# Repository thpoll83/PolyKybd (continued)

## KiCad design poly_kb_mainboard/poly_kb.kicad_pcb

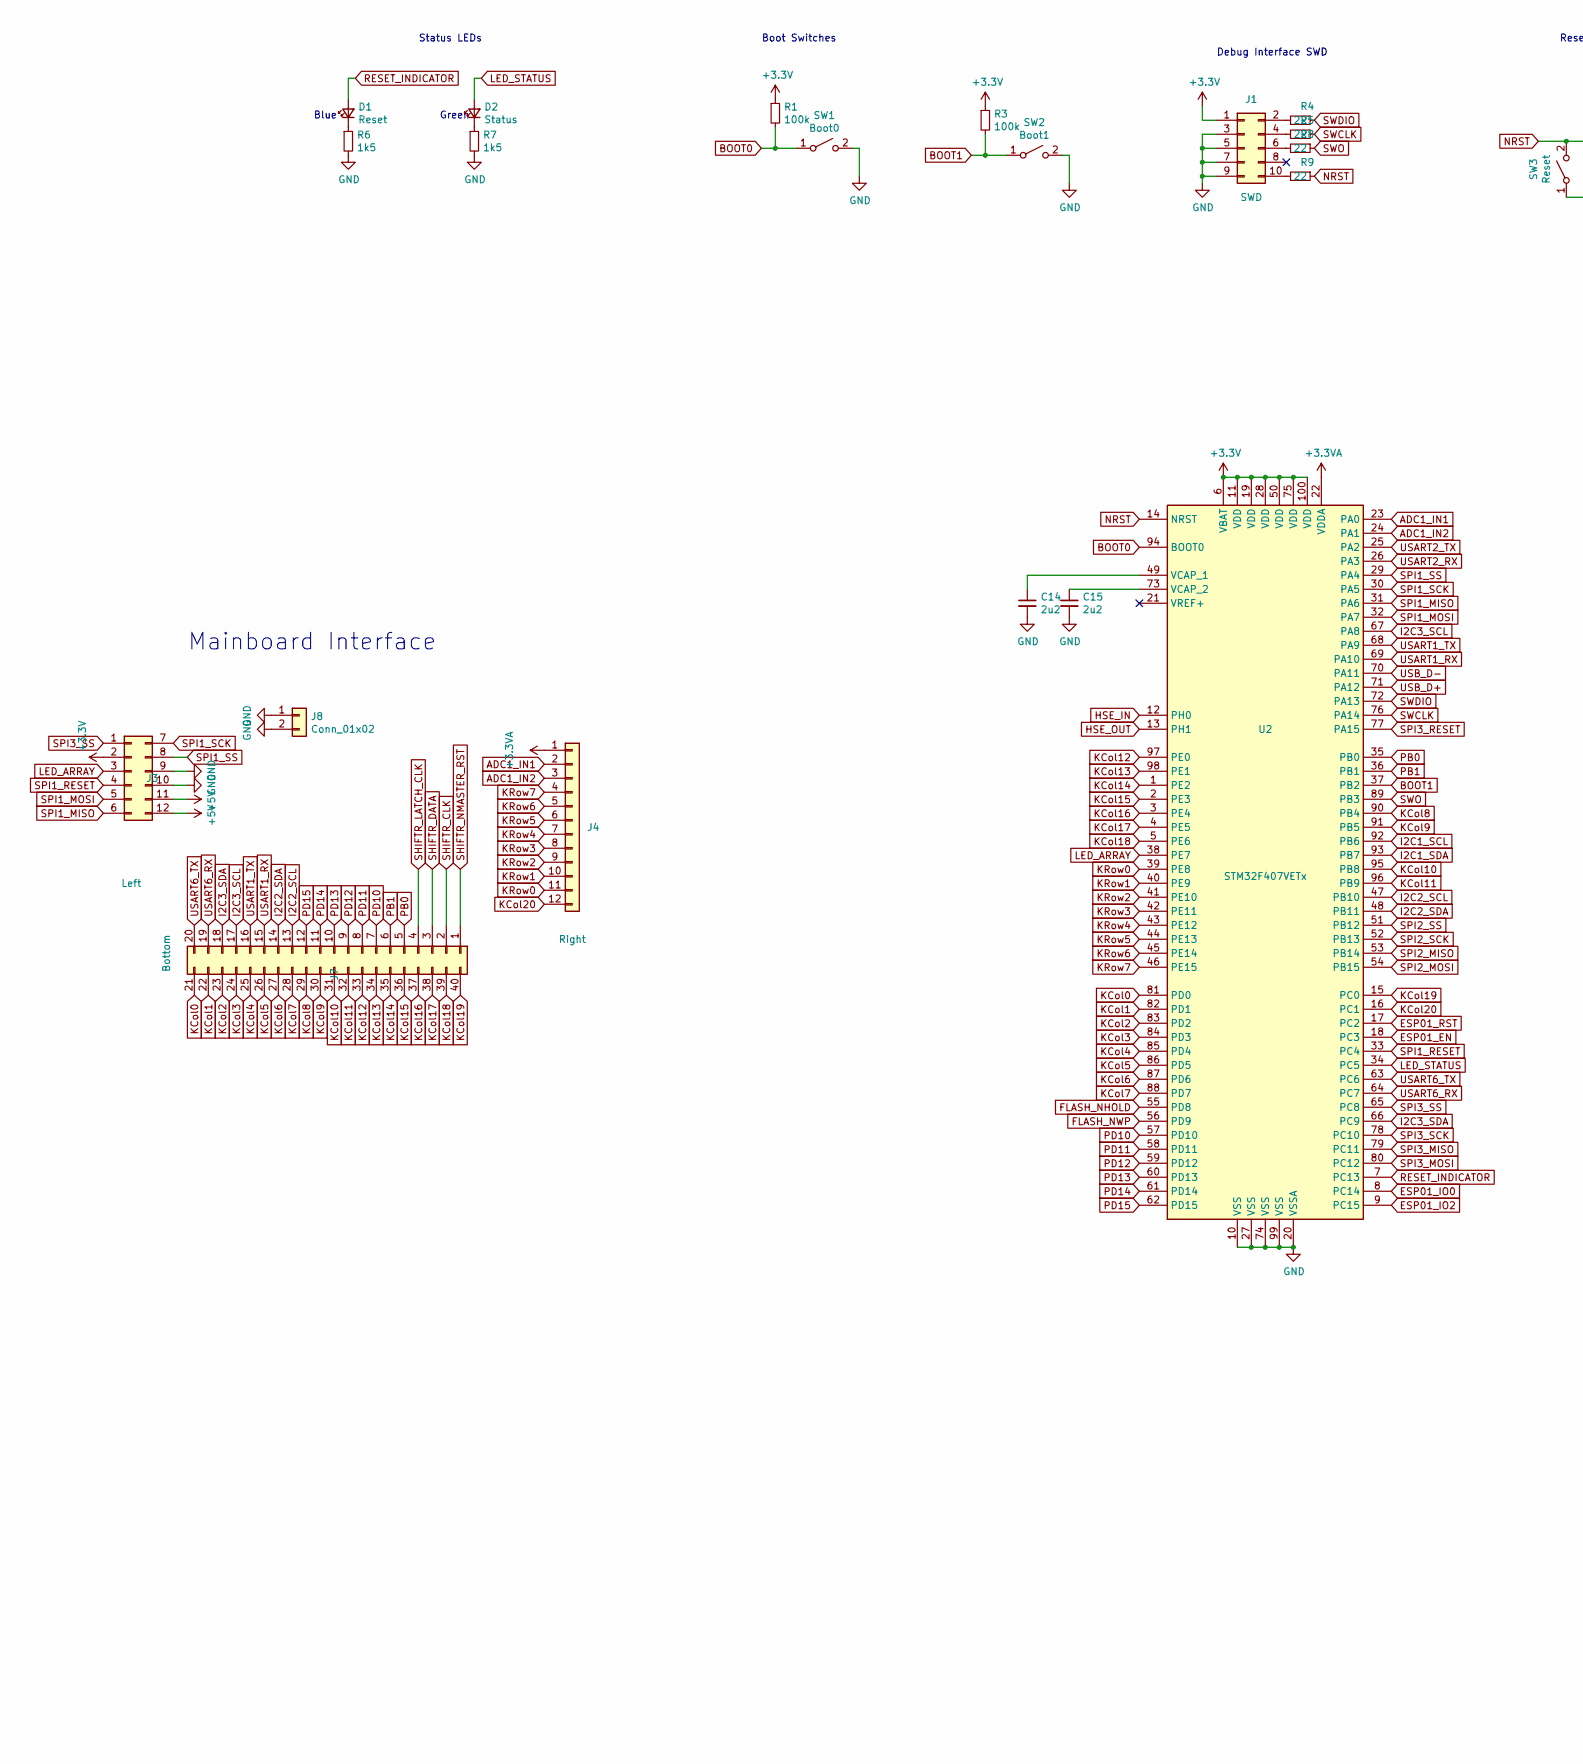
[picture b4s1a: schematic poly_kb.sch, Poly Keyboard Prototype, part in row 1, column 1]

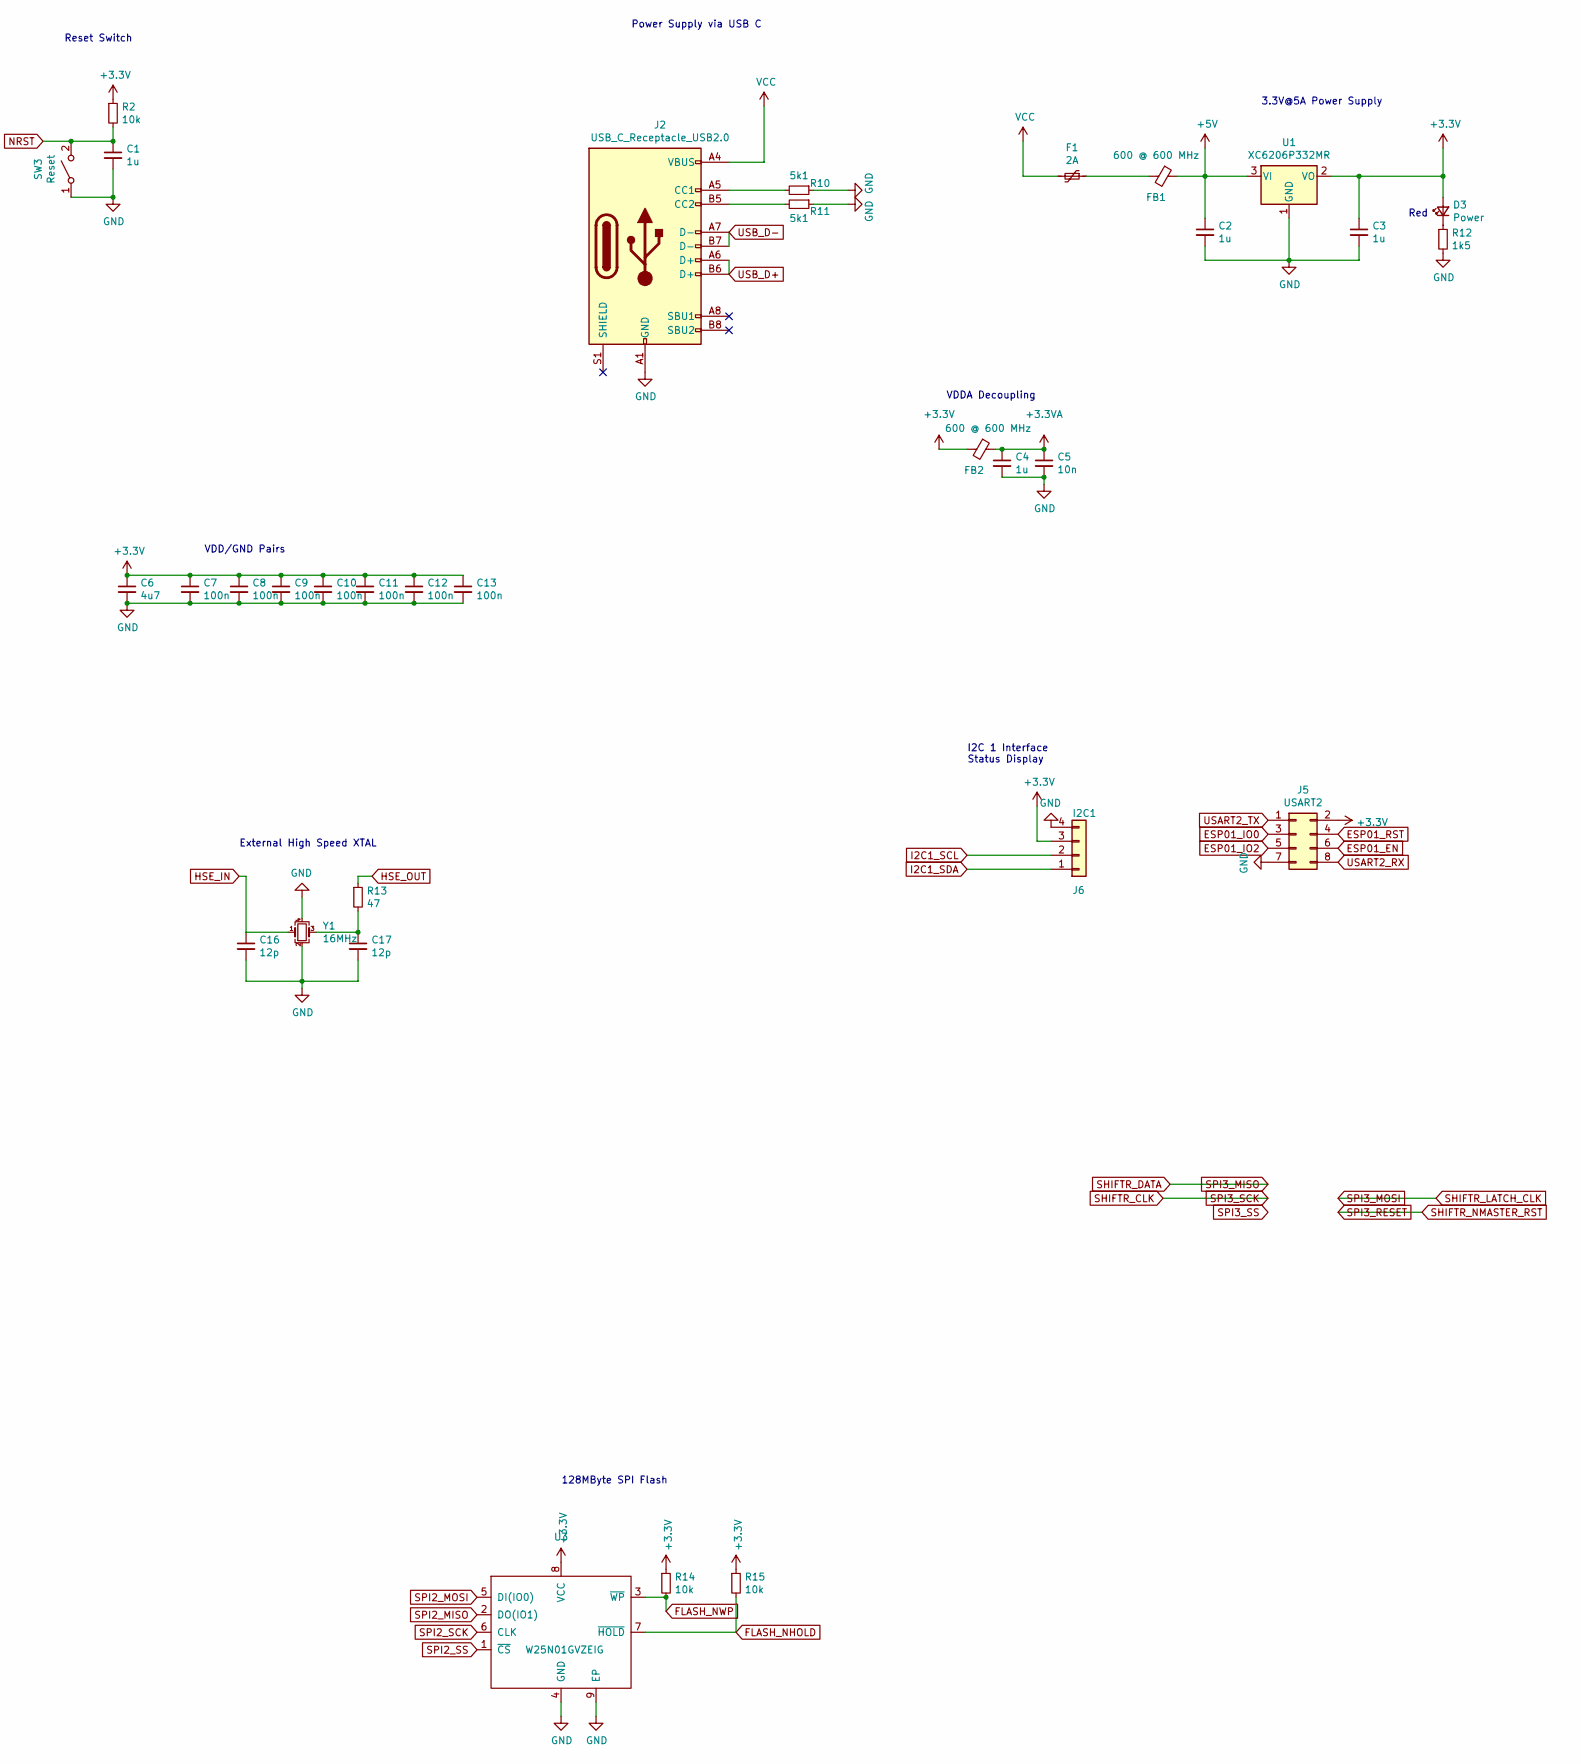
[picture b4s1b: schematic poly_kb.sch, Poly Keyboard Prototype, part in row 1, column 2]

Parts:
C1, C2, C3, C4: 1u; C_0402_1005Metric; LCSC C52923
C5: 10n; C_0402_1005Metric; LCSC C15195
C6: 4u7; C_0603_1608Metric; LCSC C19666
C7, C8, C9, C10, C11, C12, C13: 100n; C_0402_1005Metric; LCSC C1525
C14, C15: 2u2; C_0603_1608Metric; LCSC C23630
C16, C17: 12p; C_0402_1005Metric; LCSC C1547
D1: Reset; LED_0603_1608Metric; LCSC C72041
D2: Status; LED_0603_1608Metric; LCSC C72043
D3: Power; LED_0603_1608Metric; LCSC C2286
F1: 2A; Fuse_1206_3216Metric; LCSC C70085
FB1, FB2: 600 @ 600 MHz; L_0805_2012Metric; LCSC C1017
J1: SWD; SIDE-SWD
J2: USB_C_Receptacle_USB2.0; USB_C_Receptacle_HRO_TYPE-C-31-M-12; LCSC C165948
J3: Left; PinHeader_2x06_P2.54mm_Vertical; LCSC C225521
J4: Right; PinHeader_1x12_P2.54mm_Vertical; LCSC C225487
J5: USART2; PinHeader_2x04_P2.54mm_Vertical; LCSC C541854
J6: I2C1; PinHeader_1x04_P2.54mm_Vertical; LCSC C225501
J7: Bottom; PinHeader_2x20_P2.54mm_Vertical; LCSC C124383
J8: Conn_01x02; PinHeader_1x02_P2.54mm_Vertical; LCSC C464599
R1, R3: 100k; R_0402_1005Metric; LCSC C25741
R2, R14, R15: 10k; R_0402_1005Metric; LCSC C25744
R4, R5, R8, R9: 22; R_0402_1005Metric; LCSC C25092
R6, R7, R12: 1k5; R_0402_1005Metric; LCSC C25867
R10, R11: 5k1; R_0402_1005Metric; LCSC C25905
R13: 47; R_0402_1005Metric; LCSC C25118
SW1: Boot0; SW_SPST_B3U-3000P-B; LCSC C963349
SW2: Boot1; SW_SPST_B3U-3000P-B; LCSC C963349
SW3: Reset; SW_SPST_B3U-3000P-B; LCSC C963349
U1: XC6206P332MR; SOT-23; LCSC C5446
U2: STM32F407VETx; LQFP-100_14x14mm_P0.5mm; LCSC C28730
U3: W25N01GVZEIG; LCSC C88868
Y1: 16MHz; Crystal_SMD_3225-4Pin_3.2x2.5mm; LCSC C13738

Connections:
+3.3VA: C4.1, C5.1, FB2.1, J4.1, U2.22 (VDDA)
+3V3: C3.1, C6.1, C7.1, C8.1, C9.1, C10.1, C11.1, C12.1, C13.1, D3.2 (A), FB2.2, J1.1, J3.2, J5.2, J6.3, R1.1, R2.1, R3.1, R14.1, R15.1, U1.2 (VO), U2.6 (VBAT), U2.11 (VDD), U2.19 (VDD), U2.28 (VDD), U2.50 (VDD), U2.75 (VDD), U2.100 (VDD), U3.8 (VCC)
+5V: C2.1, FB1.1, J3.11, J3.12, U1.3 (VI)
ADC1_IN1: J4.2, U2.23 (PA0)
ADC1_IN2: J4.3, U2.24 (PA1)
BOOT0: R1.2, SW1.1 (A), U2.94 (BOOT0)
BOOT1: R3.2, SW2.1 (A), U2.37 (PB2)
ESP01_EN: J5.6, U2.18 (PC3)
ESP01_IO0: J5.3, U2.8 (PC14)
ESP01_IO2: J5.5, U2.9 (PC15)
ESP01_RST: J5.4, U2.17 (PC2)
FLASH_NHOLD: R15.2, U2.55 (PD8), U3.7 (~HOLD)
FLASH_NWP: R14.2, U2.56 (PD9), U3.3 (~WP)
GND: C1.2, C2.2, C3.2, C4.2, C5.2, C6.2, C7.2, C8.2, C9.2, C10.2, C11.2, C12.2, C13.2, C14.2, C15.2, C16.2, C17.2, J1.3, J1.5, J1.7, J1.9, J2.A1 (GND), J2.A12 (GND), J2.B1 (GND), J2.B12 (GND), J3.9, J3.10, J5.7, J6.4, J8.1, J8.2, R6.2, R7.2, R10.1, R11.1, R12.2, SW1.2 (B), SW2.2 (B), SW3.1 (A), U1.1 (GND), U2.10 (VSS), U2.20 (VSSA), U2.27 (VSS), U2.74 (VSS), U2.99 (VSS), U3.4 (GND), U3.9 (EP), Y1.2, Y1.4
HSE_IN: C16.1, U2.12 (PH0), Y1.1
HSE_OUT: R13.1, U2.13 (PH1)
I2C1_SCL: J6.2, U2.92 (PB6)
I2C1_SDA: J6.1, U2.93 (PB7)
I2C2_SCL: J7.13, U2.47 (PB10)
I2C2_SDA: J7.14, U2.48 (PB11)
I2C3_SCL: J7.17, U2.67 (PA8)
I2C3_SDA: J7.18, U2.66 (PC9)
KCol0: J7.21, U2.81 (PD0)
KCol1: J7.22, U2.82 (PD1)
KCol2: J7.23, U2.83 (PD2)
KCol3: J7.24, U2.84 (PD3)
KCol4: J7.25, U2.85 (PD4)
KCol5: J7.26, U2.86 (PD5)
KCol6: J7.27, U2.87 (PD6)
KCol7: J7.28, U2.88 (PD7)
KCol8: J7.29, U2.90 (PB4)
KCol9: J7.30, U2.91 (PB5)
KCol10: J7.31, U2.95 (PB8)
KCol11: J7.32, U2.96 (PB9)
KCol12: J7.33, U2.97 (PE0)
KCol13: J7.34, U2.98 (PE1)
KCol14: J7.35, U2.1 (PE2)
KCol15: J7.36, U2.2 (PE3)
KCol16: J7.37, U2.3 (PE4)
KCol17: J7.38, U2.4 (PE5)
KCol18: J7.39, U2.5 (PE6)
KCol19: J7.40, U2.15 (PC0)
KCol20: J4.12, U2.16 (PC1)
KRow0: J4.11, U2.39 (PE8)
KRow1: J4.10, U2.40 (PE9)
KRow2: J4.9, U2.41 (PE10)
KRow3: J4.8, U2.42 (PE11)
KRow4: J4.7, U2.43 (PE12)
KRow5: J4.6, U2.44 (PE13)
KRow6: J4.5, U2.45 (PE14)
KRow7: J4.4, U2.46 (PE15)
LED_ARRAY: J3.3, U2.38 (PE7)
LED_STATUS: D2.2 (A), U2.34 (PC5)
NRST: C1.1, R2.2, R9.1, SW3.2 (B), U2.14 (NRST)
unnamed: C14.1, U2.49 (VCAP_1)
unnamed: C15.1, U2.73 (VCAP_2)
unnamed: C17.1, R13.2, Y1.3
unnamed: D1.1 (K), R6.1
unnamed: D2.1 (K), R7.1
unnamed: D3.1 (K), R12.1
unnamed: F1.1, FB1.2
unnamed: J1.2, R4.2
unnamed: J1.4, R5.2
unnamed: J1.6, R8.2
unnamed: J1.10, R9.2
unnamed: J2.A5 (CC1), R10.2
unnamed: J2.B5 (CC2), R11.2
PB0: J7.5, U2.35 (PB0)
PB1: J7.6, U2.36 (PB1)
PD10: J7.7, U2.57 (PD10)
PD11: J7.8, U2.58 (PD11)
PD12: J7.9, U2.59 (PD12)
PD13: J7.10, U2.60 (PD13)
PD14: J7.11, U2.61 (PD14)
PD15: J7.12, U2.62 (PD15)
RESET_INDICATOR: D1.2 (A), U2.7 (PC13)
SHIFTR_CLK: J7.2, U2.78 (PC10)
SHIFTR_DATA: J7.3, U2.79 (PC11)
SHIFTR_LATCH_CLK: J7.4, U2.80 (PC12)
SHIFTR_NMASTER_RST: J7.1, U2.77 (PA15)
SPI1_MISO: J3.6, U2.31 (PA6)
SPI1_MOSI: J3.5, U2.32 (PA7)
SPI1_RESET: J3.4, U2.33 (PC4)
SPI1_SCK: J3.7, U2.30 (PA5)
SPI1_SS: J3.8, U2.29 (PA4)
SPI2_MISO: U2.53 (PB14), U3.2 (DO(IO1))
SPI2_MOSI: U2.54 (PB15), U3.5 (DI(IO0))
SPI2_SCK: U2.52 (PB13), U3.6 (CLK)
SPI2_SS: U2.51 (PB12), U3.1 (~CS)
SPI3_SS: J3.1, U2.65 (PC8)
SWCLK: R5.1, U2.76 (PA14)
SWDIO: R4.1, U2.72 (PA13)
SWO: R8.1, U2.89 (PB3)
USART1_RX: J7.15, U2.69 (PA10)
USART1_TX: J7.16, U2.68 (PA9)
USART2_RX: J5.8, U2.26 (PA3)
USART2_TX: J5.1, U2.25 (PA2)
USART6_RX: J7.19, U2.64 (PC7)
USART6_TX: J7.20, U2.63 (PC6)
USB_D+: J2.A6 (D+), J2.B6 (D+), U2.71 (PA12)
USB_D-: J2.A7 (D-), J2.B7 (D-), U2.70 (PA11)
VCC: F1.2, J2.A4 (VBUS), J2.A9 (VBUS), J2.B4 (VBUS), J2.B9 (VBUS)

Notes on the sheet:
VDDA Decoupling
External High Speed XTAL
Boot Switches
VDD/GND Pairs
Status LEDs
3.3V@5A Power Supply
Debug Interface SWD
I2C 1 Interface Status Display
Green
Power Supply via USB C
Reset Switch
Blue
Red
128MByte SPI Flash
Mainboard Interface

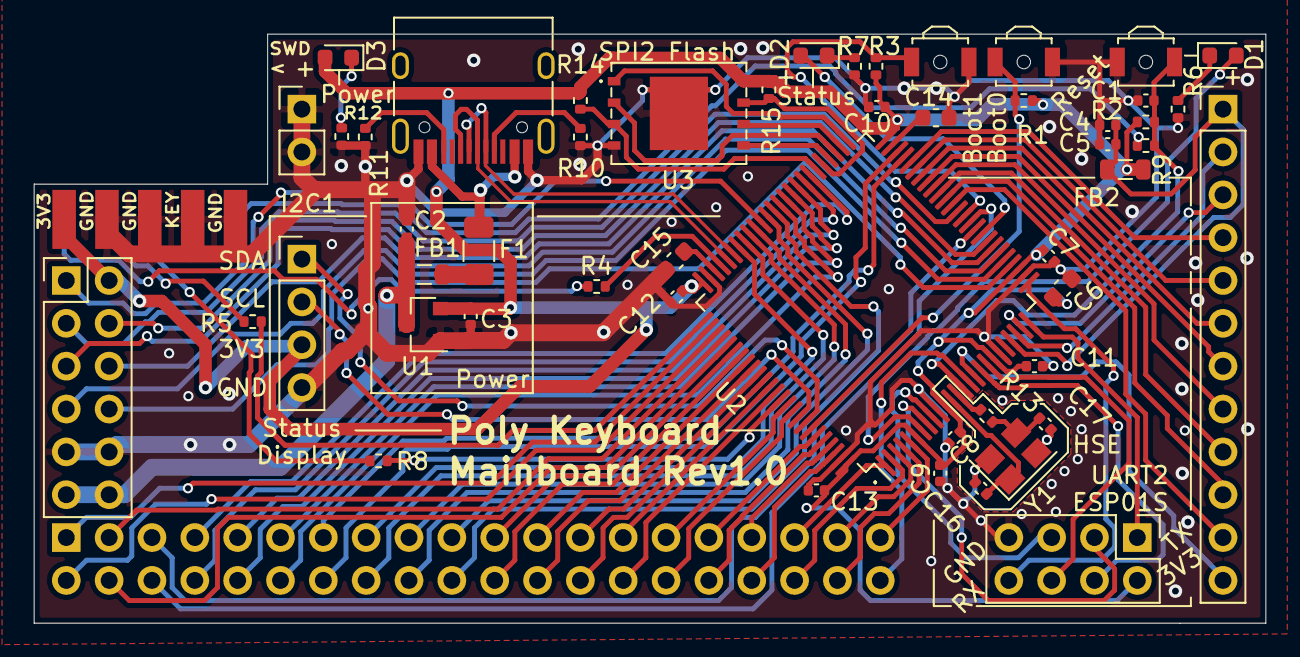
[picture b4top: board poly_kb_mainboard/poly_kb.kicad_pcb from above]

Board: 2 copper layers, 73.0 x 34.9 mm, 53 parts (1 on the bottom side), 102 nets.

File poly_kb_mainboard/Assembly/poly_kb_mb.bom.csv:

Designator,Quantity,Value,Footprint,LCSC Part #,Comment
"C1, C2, C3, C4",4,1u,C_0402_1005Metric,C52923," Unpolarized capacitor, small symbol"
C5,1,10n,C_0402_1005Metric,C15195," Unpolarized capacitor, small symbol"
C6,1,4u7,C_0603_1608Metric,C19666," Unpolarized capacitor, small symbol"
"C7, C8, C9, C10, C11, C12, C13",7,100n,C_0402_1005Metric,C1525," Unpolarized capacitor, small symbol"
"C14, C15",2,2u2,C_0603_1608Metric,C23630," Unpolarized capacitor, small symbol"
"C16, C17",2,12p,C_0402_1005Metric,C1547," Unpolarized capacitor, small symbol"
D1,1,Reset,LED_0603_1608Metric,C72041," Light emitting diode, small symbol"
D2,1,Status,LED_0603_1608Metric,C72043," Light emitting diode, small symbol"
D3,1,Power,LED_0603_1608Metric,C2286," Light emitting diode, small symbol"
F1,1,2A,Fuse_1206_3216Metric,C70085," Resettable fuse, polymeric positive temperature coefficient, small symbol"
"FB1, FB2",2,600 @ 600 MHz,L_0805_2012Metric,C1017," Ferrite bead, small symbol"
J1,1,SWD,SIDE-SWD,," Generic connector, double row, 02x05, odd/even pin numbering scheme (row 1 odd numbers, row 2 even numbers), script generated (kicad-library-utils/schlib/autogen/connector/)"
J2,1,USB_C_Receptacle_USB2.0,USB_C_Receptacle_HRO_TYPE-C-31-M-12,C165948, USB 2.0-only Type-C Receptacle connector
J3,1,Left,PinHeader_2x06_P2.54mm_Vertical,C225521," Generic connector, double row, 02x06, top/bottom pin numbering scheme (row 1: 1...pins_per_row, row2: pins_per_row+1 ... num_pins), script generated (kicad-library-utils/schlib/autogen/connector/)"
J4,1,Right,PinHeader_1x12_P2.54mm_Vertical,C225487," Generic connector, single row, 01x12, script generated (kicad-library-utils/schlib/autogen/connector/)"
J5,1,USART2,PinHeader_2x04_P2.54mm_Vertical,C541854," Generic connector, double row, 02x04, odd/even pin numbering scheme (row 1 odd numbers, row 2 even numbers), script generated (kicad-library-utils/schlib/autogen/connector/)"
J6,1,I2C1,PinHeader_1x04_P2.54mm_Vertical,C225501," Generic connector, single row, 01x04, script generated (kicad-library-utils/schlib/autogen/connector/)"
J7,1,Bottom,PinHeader_2x20_P2.54mm_Vertical,C124383," Generic connector, double row, 02x20, counter clockwise pin numbering scheme (similar to DIP packge numbering), script generated (kicad-library-utils/schlib/autogen/connector/)"
J8,1,Conn_01x02,PinHeader_1x02_P2.54mm_Vertical,C464599," Generic connector, single row, 01x02, script generated (kicad-library-utils/schlib/autogen/connector/)"
"R1, R3",2,100k,R_0402_1005Metric,C25741," Resistor, small symbol"
"R2, R14, R15",3,10k,R_0402_1005Metric,C25744," Resistor, small symbol"
"R4, R5, R8, R9",4,22,R_0402_1005Metric,C25092," Resistor, small symbol"
"R6, R7, R12",3,1k5,R_0402_1005Metric,C25867," Resistor, small symbol"
"R10, R11",2,5k1,R_0402_1005Metric,C25905," Resistor, small symbol"
R13,1,47,R_0402_1005Metric,C25118," Resistor, small symbol"
SW1,1,Boot0,SW_SPST_B3U-3000P-B,C963349, Single Pole Single Throw (SPST) switch
SW2,1,Boot1,SW_SPST_B3U-3000P-B,C963349, Single Pole Single Throw (SPST) switch
SW3,1,Reset,SW_SPST_B3U-3000P-B,C963349, Single Pole Single Throw (SPST) switch
U1,1,XC6206P332MR,SOT-23,C5446," Positive 60-250mA Low Dropout Regulator, Fixed Output, SOT-23"
U2,1,STM32F407VETx,LQFP-100_14x14mm_P0.5mm,C28730," ARM Cortex-M4 MCU, 512KB flash, 128KB RAM, 168MHz, 1.8-3.6V, 82 GPIO, LQFP-100"
U3,1,W25N01GVZEIG,W25N01GVZEIG,C88868, 
Y1,1,16MHz,Crystal_SMD_3225-4Pin_3.2x2.5mm,C13738," Four pin crystal, GND on pins 2 and 4, small symbol"

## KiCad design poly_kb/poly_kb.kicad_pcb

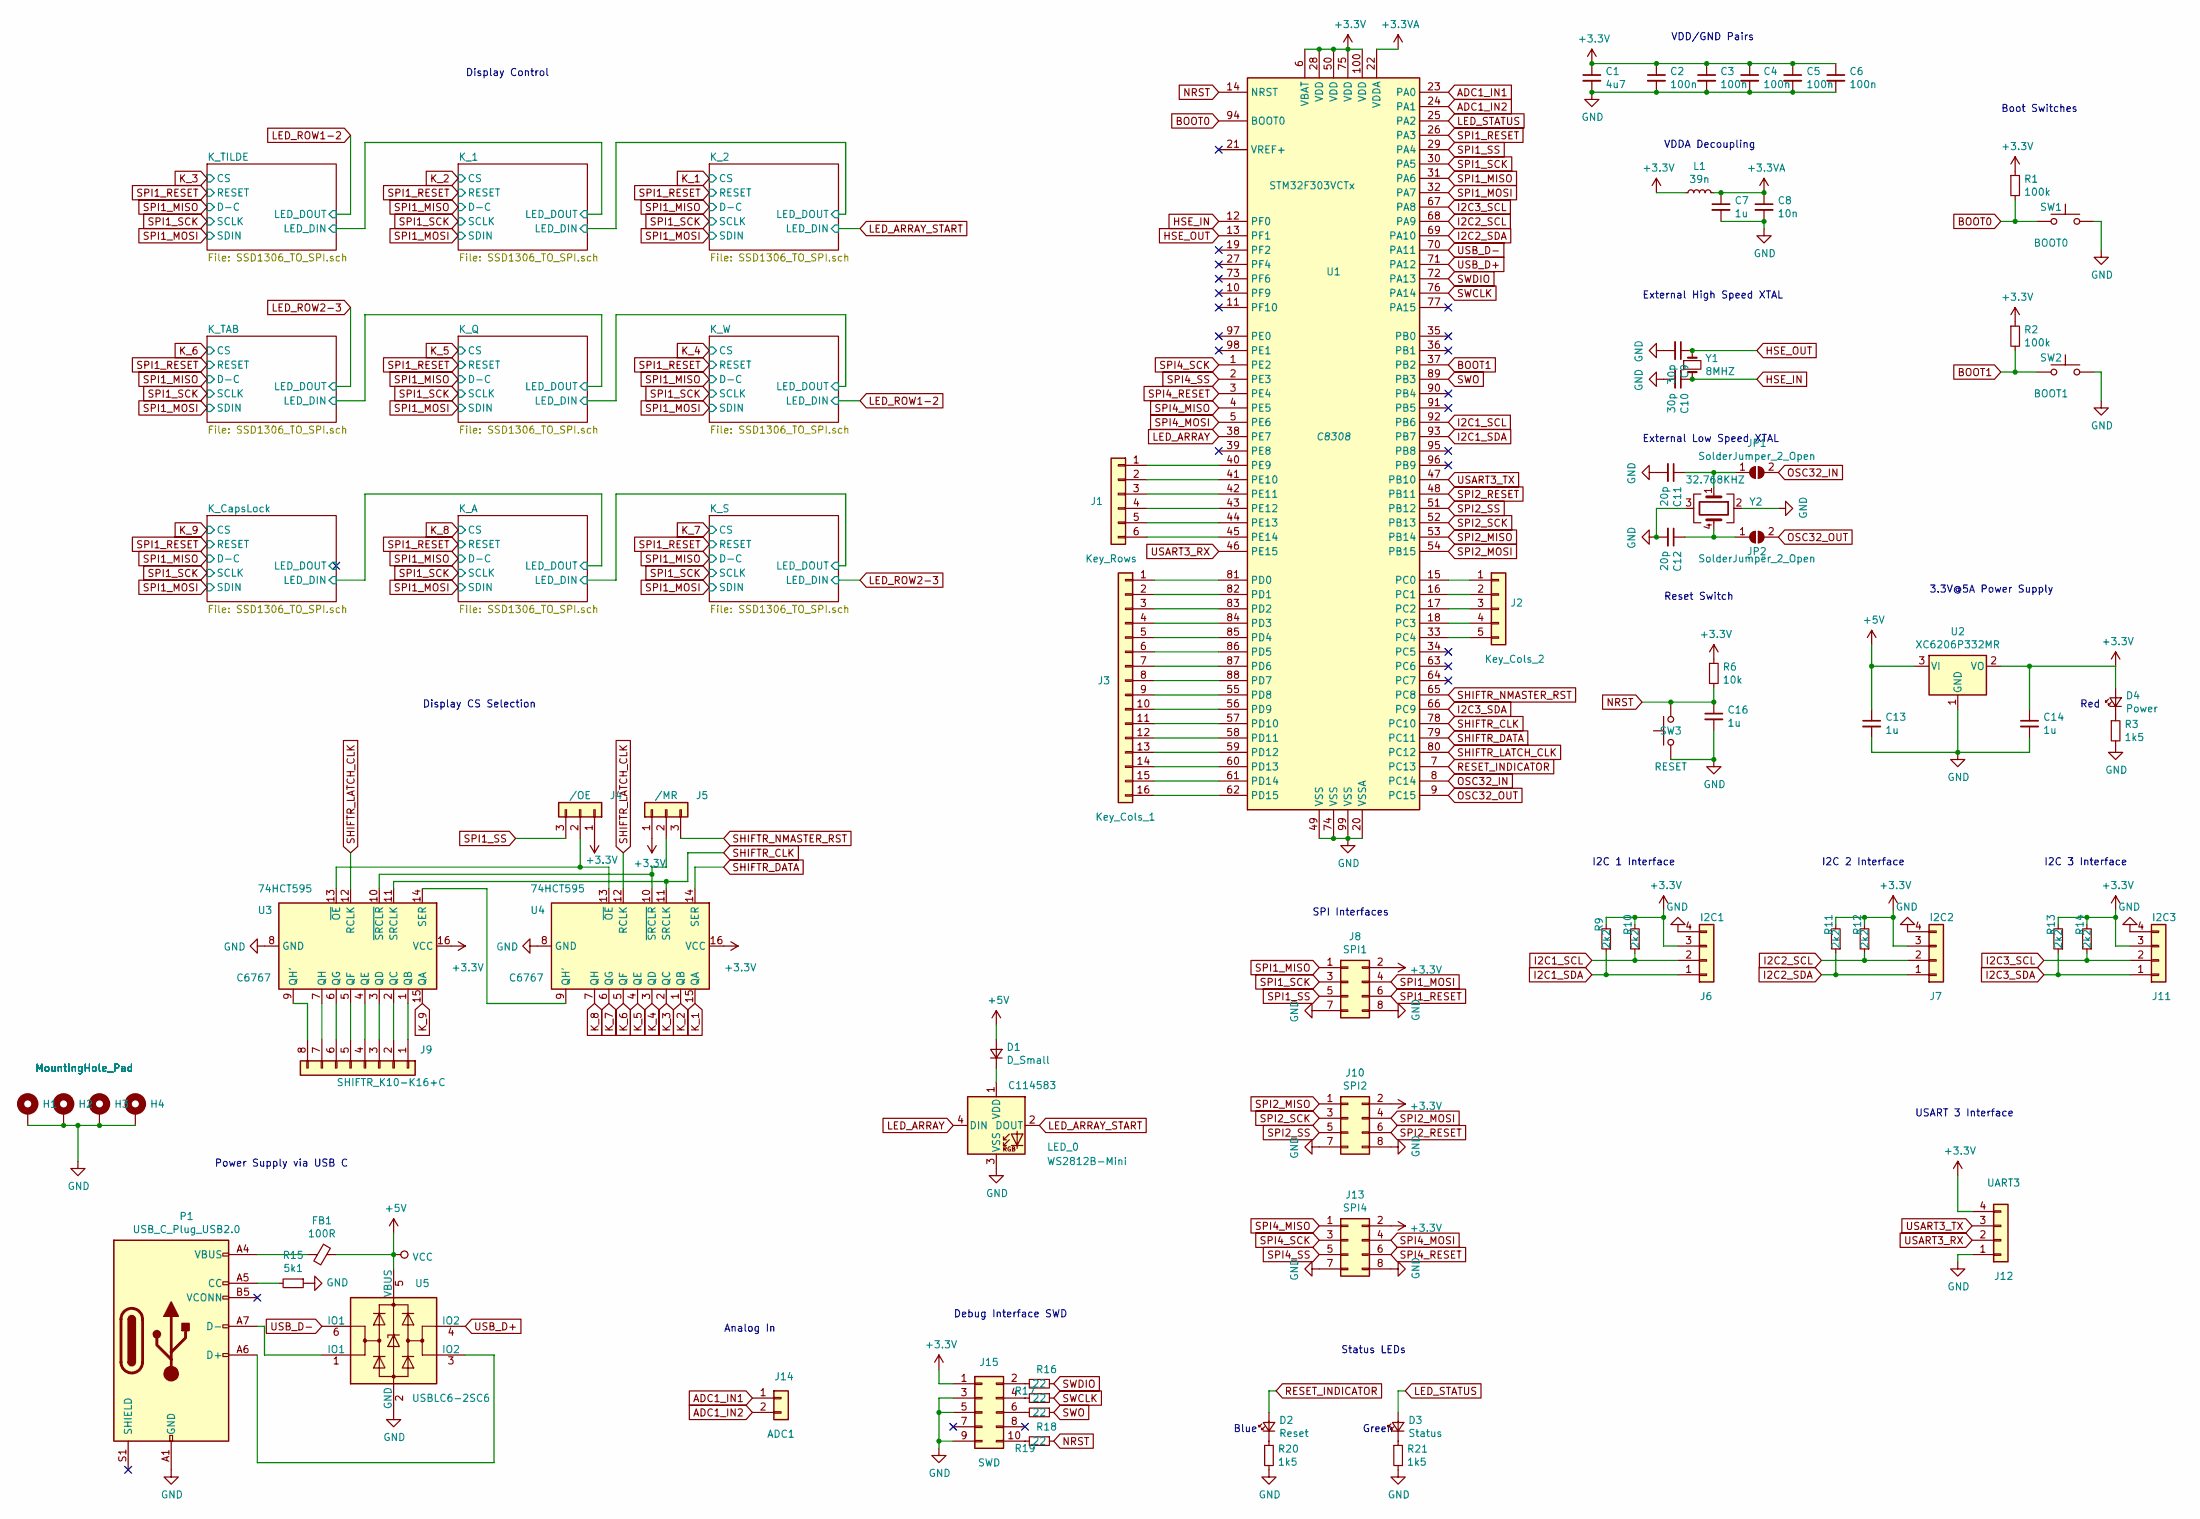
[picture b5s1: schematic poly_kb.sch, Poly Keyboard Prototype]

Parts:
C1: 4u7; C_0603_1608Metric; LCSC C19666
C2, C3, C4, C5, C6: 100n; C_0402_1005Metric; LCSC C1525
C7, C13, C14, C16: 1u; C_0402_1005Metric; LCSC C52923
C8: 10n; C_0402_1005Metric; LCSC C15195
C9, C10: 30p; C_0402_1005Metric; LCSC C1570
C11, C12: 20p; C_0603_1608Metric; LCSC C1603
D1: D_Small; D_SOD-123F; LCSC C64898
D2: Reset; LED_0603_1608Metric; LCSC C72041
D3: Status; LED_0603_1608Metric; LCSC C72043
D4: Power; LED_0603_1608Metric; LCSC C2286
FB1: 100R; L_0805_2012Metric; LCSC C1015
H1, H2, H3, H4: MountingHole_Pad; MountingHole_4.3mm_M4_Pad_Via
J1: Key_Rows; PinHeader_1x06_P2.54mm_Vertical
J2: Key_Cols_2; PinHeader_1x05_P2.54mm_Vertical
J3: Key_Cols_1; PinHeader_1x16_P2.54mm_Vertical
J4: /OE; PinHeader_1x03_P2.54mm_Vertical
J5: /MR; PinHeader_1x03_P2.54mm_Vertical
J6: I2C1; PinHeader_1x04_P2.54mm_Vertical
J7: I2C2; PinHeader_1x04_P2.54mm_Vertical
J8: SPI1; PinHeader_2x04_P2.54mm_Vertical
J9: SHIFTR_K10-K16+C; PinHeader_1x08_P2.54mm_Vertical
J10: SPI2; PinHeader_2x04_P2.54mm_Vertical
J11: I2C3; PinHeader_1x04_P2.54mm_Vertical
J12: UART3; PinHeader_1x04_P2.54mm_Vertical
J13: SPI4; PinHeader_2x04_P2.54mm_Vertical
J14: ADC1; PinHeader_1x02_P2.54mm_Vertical
J15: SWD; PinHeader_2x05_P2.54mm_Vertical
JP1, JP2: SolderJumper_2_Open; SolderJumper-2_P1.3mm_Open_TrianglePad1.0x1.5mm
L1: 39n; L_0402_1005Metric; LCSC C26443
LED_0: WS2812B-Mini; LCSC C114583
P1: USB_C_Plug_USB2.0; USB_C_Receptacle_Palconn_UTC16-G; LCSC C393939
R1, R2: 100k; R_0603_1608Metric; LCSC C25803
R3, R20, R21: 1k5; R_0805_2012Metric; LCSC C4310
R6: 10k; R_0402_1005Metric; LCSC C25744
R9, R10, R11, R12, R13, R14: 2k2; R_0805_2012Metric; LCSC C17521
R15: 5k1; R_0603_1608Metric; LCSC C23186
R16, R17, R18, R19: 22; R_0805_2012Metric; LCSC C17561
SW1: BOOT0; Switch_THT
SW2: BOOT1; Switch_THT
SW3: RESET; Switch_THT
U1: STM32F303VCTx; LQFP-100_14x14mm_P0.5mm; LCSC C8308
U2: XC6206P332MR; SOT-23; LCSC C5446
U3, U4: 74HCT595; SOIC-16_3.9x9.9mm_P1.27mm; LCSC C6767
U5: USBLC6-2SC6; SOT-23-6; LCSC C7519
Y1: 8MHZ; Crystal_SMD_5032-2Pin_5.0x3.2mm; LCSC C115962
Y2: 32.768KHZ; SMD-0832_4P; LCSC C145166

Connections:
+3.3VA: C7.1, C8.1, L1.2, U1.22 (VDDA)
+3V3: C1.1, C2.1, C3.1, C4.1, C5.1, C6.1, C14.1, D4.2 (A), J4.1, J5.1, J6.3, J7.3, J8.2, J10.2, J11.3, J12.4, J13.2, J15.1, L1.1, R1.1, R2.1, R6.1, R9.2, R10.2, R11.2, R12.2, R13.2, R14.2, U1.6 (VBAT), U1.28 (VDD), U1.50 (VDD), U1.75 (VDD), U1.100 (VDD), U2.2 (VO), U3.16 (VCC), U4.16 (VCC); also elsewhere on the board
+5V: C13.1, D1.2 (A), FB1.1, U2.3 (VI), U5.5 (VBUS); also elsewhere on the board
ADC1_IN1: J14.1, U1.23 (PA0)
ADC1_IN2: J14.2, U1.24 (PA1)
BOOT0: R1.2, SW1.1, U1.94 (BOOT0)
BOOT1: R2.2, SW2.1, U1.37 (PB2)
GND: C1.2, C2.2, C3.2, C4.2, C5.2, C6.2, C7.2, C8.2, C9.2, C10.2, C11.2, C12.2, C13.2, C14.2, C16.2, H1.1, H2.1, H3.1, H4.1, J6.4, J7.4, J8.7, J8.8, J10.7, J10.8, J11.4, J12.1, J13.7, J13.8, J15.3, J15.5, J15.9, LED_0.3 (VSS), P1.A1 (GND), P1.A12 (GND), P1.B1 (GND), P1.B12 (GND), R3.2, R15.1, R20.2, R21.2, SW1.2, SW2.2, SW3.2, U1.20 (VSSA), U1.49 (VSS), U1.74 (VSS), U1.99 (VSS), U2.1 (GND), U3.8 (GND), U4.8 (GND), U5.2 (GND), Y2.2, Y2.3; also elsewhere on the board
HSE_IN: C10.1, U1.12 (PF0), Y1.2
HSE_OUT: C9.1, U1.13 (PF1), Y1.1
I2C1_SCL: J6.2, R10.1, U1.92 (PB6)
I2C1_SDA: J6.1, R9.1, U1.93 (PB7)
I2C2_SCL: J7.2, R12.1, U1.68 (PA9)
I2C2_SDA: J7.1, R11.1, U1.69 (PA10)
I2C3_SCL: J11.2, R14.1, U1.67 (PA8)
I2C3_SDA: J11.1, R13.1, U1.66 (PC9)
K_1: U4.15 (QA); also elsewhere on the board
K_2: U4.1 (QB); also elsewhere on the board
K_3: U4.2 (QC); also elsewhere on the board
K_4: U4.3 (QD); also elsewhere on the board
K_5: U4.4 (QE); also elsewhere on the board
K_6: U4.5 (QF); also elsewhere on the board
K_7: U4.6 (QG); also elsewhere on the board
K_8: U4.7 (QH); also elsewhere on the board
K_9: U3.15 (QA); also elsewhere on the board
LED_ARRAY: LED_0.4 (DIN), U1.38 (PE7)
LED_ARRAY_START: LED_0.2 (DOUT); also elsewhere on the board
LED_STATUS: D3.2 (A), U1.25 (PA2)
NRST: C16.1, R6.2, R19.1, SW3.1, U1.14 (NRST)
unnamed: C11.1, JP1.1 (A), Y2.1
unnamed: C12.1, JP2.1 (A), Y2.4
unnamed: D1.1 (K), LED_0.1 (VDD)
unnamed: D2.1 (K), R20.1
unnamed: D3.1 (K), R21.1
unnamed: D4.1 (K), R3.1
unnamed: FB1.2, P1.A4 (VBUS), P1.A9 (VBUS), P1.B4 (VBUS), P1.B9 (VBUS)
unnamed: J1.1, U1.40 (PE9)
unnamed: J1.2, U1.41 (PE10)
unnamed: J1.3, U1.42 (PE11)
unnamed: J1.4, U1.43 (PE12)
unnamed: J1.5, U1.44 (PE13)
unnamed: J1.6, U1.45 (PE14)
unnamed: J2.1, U1.15 (PC0)
unnamed: J2.2, U1.16 (PC1)
unnamed: J2.3, U1.17 (PC2)
unnamed: J2.4, U1.18 (PC3)
unnamed: J2.5, U1.33 (PC4)
unnamed: J3.1, U1.81 (PD0)
unnamed: J3.2, U1.82 (PD1)
unnamed: J3.3, U1.83 (PD2)
unnamed: J3.4, U1.84 (PD3)
unnamed: J3.5, U1.85 (PD4)
unnamed: J3.6, U1.86 (PD5)
unnamed: J3.7, U1.87 (PD6)
unnamed: J3.8, U1.88 (PD7)
unnamed: J3.9, U1.55 (PD8)
unnamed: J3.10, U1.56 (PD9)
unnamed: J3.11, U1.57 (PD10)
unnamed: J3.12, U1.58 (PD11)
unnamed: J3.13, U1.59 (PD12)
unnamed: J3.14, U1.60 (PD13)
unnamed: J3.15, U1.61 (PD14)
unnamed: J3.16, U1.62 (PD15)
unnamed: J4.2, U3.13 (~OE), U4.13 (~OE)
unnamed: J5.2, U3.10 (~SRCLR), U4.10 (~SRCLR)
unnamed: J9.1, U3.1 (QB)
unnamed: J9.2, U3.2 (QC)
unnamed: J9.3, U3.3 (QD)
unnamed: J9.4, U3.4 (QE)
unnamed: J9.5, U3.5 (QF)
unnamed: J9.6, U3.6 (QG)
unnamed: J9.7, U3.7 (QH)
unnamed: J9.8, U3.9 (QH')
unnamed: J15.2, R16.2
unnamed: J15.4, R17.2
unnamed: J15.6, R18.2
unnamed: J15.10, R19.2
unnamed: P1.A5 (CC), R15.2
unnamed: P1.A6 (D+), U5.3 (IO2)
unnamed: P1.A7 (D-), U5.1 (IO1)
unnamed: U3.14 (SER), U4.9 (QH')
OSC32_IN: JP1.2 (B), U1.8 (PC14)
OSC32_OUT: JP2.2 (B), U1.9 (PC15)
RESET_INDICATOR: D2.2 (A), U1.7 (PC13)
SHIFTR_CLK: U1.78 (PC10), U3.11 (SRCLK), U4.11 (SRCLK)
SHIFTR_DATA: U1.79 (PC11), U4.14 (SER)
SHIFTR_LATCH_CLK: U1.80 (PC12), U3.12 (RCLK), U4.12 (RCLK)
SHIFTR_NMASTER_RST: J5.3, U1.65 (PC8)
SPI1_MISO: J8.1, U1.31 (PA6); also elsewhere on the board
SPI1_MOSI: J8.4, U1.32 (PA7); also elsewhere on the board
SPI1_RESET: J8.6, U1.26 (PA3); also elsewhere on the board
SPI1_SCK: J8.3, U1.30 (PA5); also elsewhere on the board
SPI1_SS: J4.3, J8.5, U1.29 (PA4)
SPI2_MISO: J10.1, U1.53 (PB14)
SPI2_MOSI: J10.4, U1.54 (PB15)
SPI2_RESET: J10.6, U1.48 (PB11)
SPI2_SCK: J10.3, U1.52 (PB13)
SPI2_SS: J10.5, U1.51 (PB12)
SPI4_MISO: J13.1, U1.4 (PE5)
SPI4_MOSI: J13.4, U1.5 (PE6)
SPI4_RESET: J13.6, U1.3 (PE4)
SPI4_SCK: J13.3, U1.1 (PE2)
SPI4_SS: J13.5, U1.2 (PE3)
SWCLK: R17.1, U1.76 (PA14)
SWDIO: R16.1, U1.72 (PA13)
SWO: R18.1, U1.89 (PB3)
USART3_RX: J12.2, U1.46 (PE15)
USART3_TX: J12.3, U1.47 (PB10)
USB_D+: U1.71 (PA12), U5.4 (IO2)
USB_D-: U1.70 (PA11), U5.6 (IO1)

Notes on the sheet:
VDDA Decoupling
External High Speed XTAL
Boot Switches
VDD/GND Pairs
Status LEDs
3.3V@5A Power Supply
Debug Interface SWD
I2C 2 Interface
I2C 1 Interface
I2C 3 Interface
Green
SPI Interfaces
USART 3 Interface
Power Supply via USB C
Display CS Selection
Display Control
Analog In
Reset Switch
Blue
External Low Speed XTAL
Red

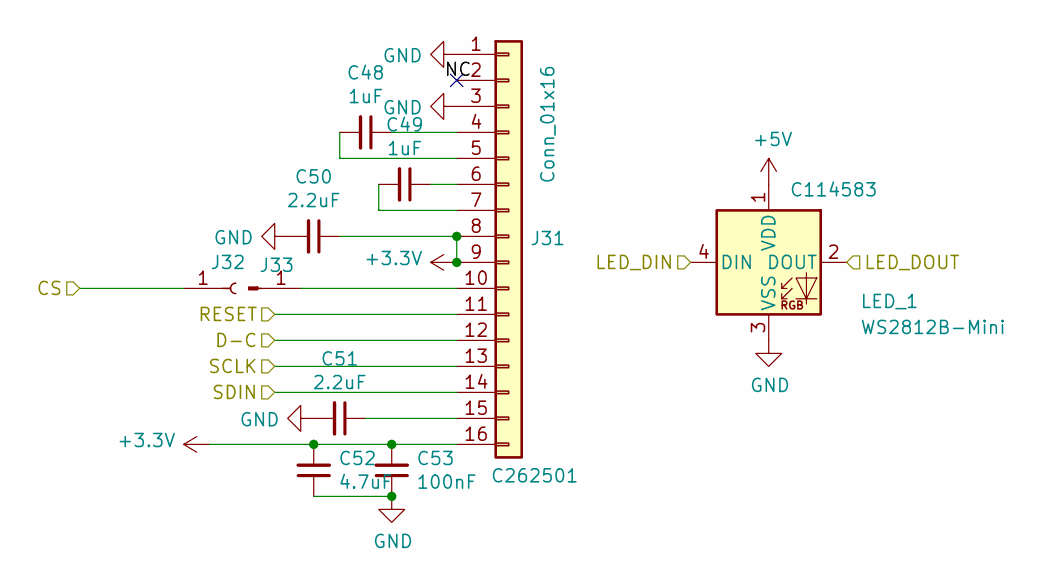
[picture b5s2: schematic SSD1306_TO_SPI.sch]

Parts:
C18, C19: 1uF; C_0805_2012Metric; LCSC C28323
C20, C21: 2.2uF; C_0805_2012Metric; LCSC C49217
C22: 4.7uF; C_0805_2012Metric; LCSC C1779
C23: 100nF; C_0805_2012Metric; LCSC C49678
J16: Conn_01x16; FPC_16_AFC11-S16ICA-00; LCSC C262501
J17: Conn_01x01_Female; PinHeader_1x01_P1.00mm_Vertical
J21: Conn_01x01_Male; PinHeader_1x01_P1.00mm_Vertical
LED_5: WS2812B-Mini; LCSC C114583

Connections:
+3V3: C20.1, C22.2, C23.2, J16.8, J16.9, J16.16; also elsewhere on the board
+5V: LED_5.1 (VDD); also elsewhere on the board
/K_Q/LED_DIN: LED_5.4 (DIN); also elsewhere on the board
/K_TAB/LED_DIN: LED_5.2 (DOUT); also elsewhere on the board
GND: C20.2, C21.2, C22.1, C23.1, J16.1, J16.3, LED_5.3 (VSS); also elsewhere on the board
K_5: J17.1; also elsewhere on the board
unnamed: C18.1, J16.4
unnamed: C18.2, J16.5
unnamed: C19.1, J16.6
unnamed: C19.2, J16.7
unnamed: C21.1, J16.15
SPI1_MISO: J16.12; also elsewhere on the board
SPI1_MOSI: J16.14; also elsewhere on the board
SPI1_RESET: J16.11; also elsewhere on the board
SPI1_SCK: J16.13; also elsewhere on the board

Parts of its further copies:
C24, C25, C30, C31, C36, C37, C42, C43, C48, C49, C54, C55, C60, C61, C66, C67: 1uF; C_0805_2012Metric; LCSC C28323
C26, C27, C32, C33, C38, C39, C44, C45, C50, C51, C56, C57, C62, C63, C68, C69: 2.2uF; C_0805_2012Metric; LCSC C49217
C28, C34, C40, C46, C52, C58, C64, C70: 4.7uF; C_0805_2012Metric; LCSC C1779
C29, C35, C41, C47, C53, C59, C65, C71: 100nF; C_0805_2012Metric; LCSC C49678
J18, J24, J27, J30, J33, J36, J39, J42: Conn_01x01_Male; PinHeader_1x01_P1.00mm_Vertical
J19, J22, J25, J28, J31, J34, J37, J40: Conn_01x16; FPC_16_AFC11-S16ICA-00; LCSC C262501
J20, J23, J26, J29, J32, J35, J38, J41: Conn_01x01_Female; PinHeader_1x01_P1.00mm_Vertical
LED_1, LED_2, LED_3, LED_4, LED_6, LED_7, LED_8, LED_9: WS2812B-Mini; LCSC C114583

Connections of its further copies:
+3V3: C26.1, C28.2, C29.2, C32.1, C34.2, C35.2, C38.1, C40.2, C41.2, C44.1, C46.2, C47.2, C50.1, C52.2, C53.2, C56.1, C58.2, C59.2, C62.1, C64.2, C65.2, C68.1, C70.2, C71.2, J19.8, J19.9, J19.16, J22.8, J22.9, J22.16, J25.8, J25.9, J25.16, J28.8, J28.9, J28.16, J31.8, J31.9, J31.16, J34.8, J34.9, J34.16, J37.8, J37.9, J37.16, J40.8, J40.9, J40.16; also elsewhere on the board
+5V: LED_1.1 (VDD), LED_2.1 (VDD), LED_3.1 (VDD), LED_4.1 (VDD), LED_6.1 (VDD), LED_7.1 (VDD), LED_8.1 (VDD), LED_9.1 (VDD); also elsewhere on the board
/K_1/LED_DIN: LED_2.4 (DIN), LED_3.2 (DOUT)
/K_A/LED_DIN: LED_8.4 (DIN), LED_9.2 (DOUT)
/K_CapsLock/LED_DIN: LED_7.4 (DIN), LED_8.2 (DOUT)
/K_Q/LED_DIN: LED_6.2 (DOUT); also elsewhere on the board
/K_TAB/LED_DIN: LED_4.4 (DIN); also elsewhere on the board
/K_TILDE/LED_DIN: LED_1.4 (DIN), LED_2.2 (DOUT)
GND: C26.2, C27.2, C28.1, C29.1, C32.2, C33.2, C34.1, C35.1, C38.2, C39.2, C40.1, C41.1, C44.2, C45.2, C46.1, C47.1, C50.2, C51.2, C52.1, C53.1, C56.2, C57.2, C58.1, C59.1, C62.2, C63.2, C64.1, C65.1, C68.2, C69.2, C70.1, C71.1, J19.1, J19.3, J22.1, J22.3, J25.1, J25.3, J28.1, J28.3, J31.1, J31.3, J34.1, J34.3, J37.1, J37.3, J40.1, J40.3, LED_1.3 (VSS), LED_2.3 (VSS), LED_3.3 (VSS), LED_4.3 (VSS), LED_6.3 (VSS), LED_7.3 (VSS), LED_8.3 (VSS), LED_9.3 (VSS); also elsewhere on the board
K_1: J29.1; also elsewhere on the board
K_2: J26.1; also elsewhere on the board
K_3: J32.1; also elsewhere on the board
K_4: J20.1; also elsewhere on the board
K_6: J23.1; also elsewhere on the board
K_7: J38.1; also elsewhere on the board
K_8: J35.1; also elsewhere on the board
K_9: J41.1; also elsewhere on the board
LED_ARRAY_START: LED_3.4 (DIN); also elsewhere on the board
LED_ROW1-2: LED_1.2 (DOUT), LED_6.4 (DIN)
LED_ROW2-3: LED_4.2 (DOUT), LED_9.4 (DIN)
unnamed: C24.1, J19.4
unnamed: C24.2, J19.5
unnamed: C25.1, J19.6
unnamed: C25.2, J19.7
unnamed: C27.1, J19.15
unnamed: C30.1, J22.4
unnamed: C30.2, J22.5
unnamed: C31.1, J22.6
unnamed: C31.2, J22.7
unnamed: C33.1, J22.15
unnamed: C36.1, J25.4
unnamed: C36.2, J25.5
unnamed: C37.1, J25.6
unnamed: C37.2, J25.7
unnamed: C39.1, J25.15
unnamed: C42.1, J28.4
unnamed: C42.2, J28.5
unnamed: C43.1, J28.6
unnamed: C43.2, J28.7
unnamed: C45.1, J28.15
unnamed: C48.1, J31.4
unnamed: C48.2, J31.5
unnamed: C49.1, J31.6
unnamed: C49.2, J31.7
unnamed: C51.1, J31.15
unnamed: C54.1, J34.4
unnamed: C54.2, J34.5
unnamed: C55.1, J34.6
unnamed: C55.2, J34.7
unnamed: C57.1, J34.15
unnamed: C60.1, J37.4
unnamed: C60.2, J37.5
unnamed: C61.1, J37.6
unnamed: C61.2, J37.7
unnamed: C63.1, J37.15
unnamed: C66.1, J40.4
unnamed: C66.2, J40.5
unnamed: C67.1, J40.6
unnamed: C67.2, J40.7
unnamed: C69.1, J40.15
unnamed: J22.10, J24.1
unnamed: J25.10, J27.1
unnamed: J28.10, J30.1
unnamed: J31.10, J33.1
unnamed: J34.10, J36.1
unnamed: J37.10, J39.1
unnamed: J40.10, J42.1
SPI1_MISO: J19.12, J22.12, J25.12, J28.12, J31.12, J34.12, J37.12, J40.12; also elsewhere on the board
SPI1_MOSI: J19.14, J22.14, J25.14, J28.14, J31.14, J34.14, J37.14, J40.14; also elsewhere on the board
SPI1_RESET: J19.11, J22.11, J25.11, J28.11, J31.11, J34.11, J37.11, J40.11; also elsewhere on the board
SPI1_SCK: J19.13, J22.13, J25.13, J28.13, J31.13, J34.13, J37.13, J40.13; also elsewhere on the board

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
